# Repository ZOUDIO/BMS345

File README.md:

# BMS345
Protection and charging module for 3/4/5S lithium batteries 
This project is fully open-source and may be used commercially.
ZOUDIO is only liable for products of its own production.

Based on:
Texas Instruments BQ77915 primary battery protector
Texas Instruments BQ24650 battery charger

Configuration is set by using the onboard header. 

Specifications (for more details and instructions, refer to the PDF datasheet)
-	Overvoltage:				4.2V ±10mV, delay 1S
-	Undervoltage: 			2.9V ±18mV, delay 1S
-	Cell balancing 			4mA per cell
-	Maximum continuous discharge:	10A
-	Overcurrent protection: 		15A, delay 180mS
-	Short-circuit protection: 		30A, delay 1mS
-	Recovery after fault event: 		Attach charger
-	Open cell/wire detection:		4.5S delay
-	Power consumption: 			8μA typical
-	Charging current:			1A
-	Charging voltage:			4.05V per cell
-	MPPT voltage:			17.5V
-	Operating temperature: 		-40 to 85 °C
-	Dimensions (WxHxD):		71x38x15mm

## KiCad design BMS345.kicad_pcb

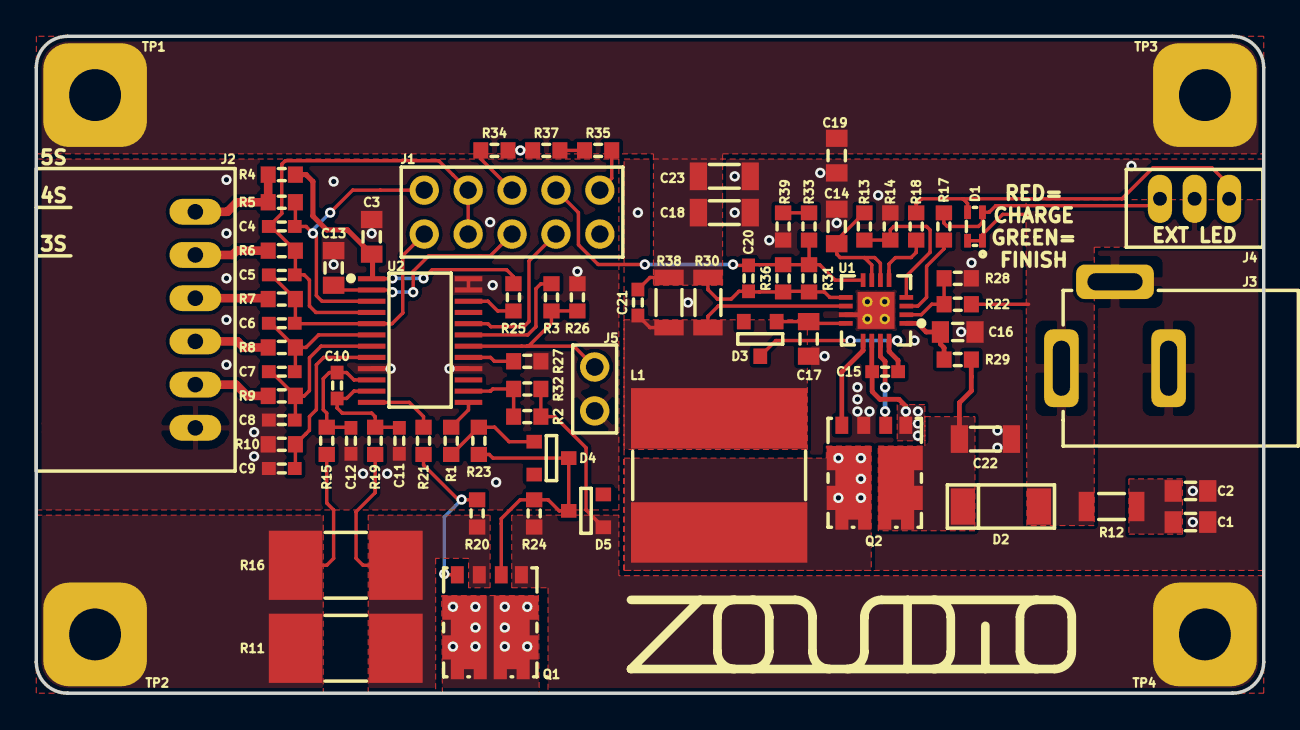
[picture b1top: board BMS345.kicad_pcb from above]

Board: 2 copper layers, 71.0 x 38.0 mm, 82 parts (0 on the bottom side), 54 nets.

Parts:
C1, C2, C3, C13, C14, C16, C17, C19: 1u; C0805
C4, C5, C6, C7, C8, C9, C10, C11, C12, C15, C21: 100n; C0603
C18, C22, C23: 10u; C1206
C20: 18p; C0603
D1: RED/GREEN; KingBright_KPTB
D2: Schottky; SOD-128
D3, D4: Schottky; SOT-23Z
D5: 10V; SOT-23Z
J1: CONFIG; PinHeader_2x05_P2.54mm_Vertical
J2: BATT; JSTXH_S6B
J3: DC Jack; DC_Jack
J4: EXTLED; JSTPH_3P
J5: NTC; 2P_2.54mm_header
L1: 10u; SRN1060
Logo1: ZOUDIO; ZOUDIO25mm
Q1, Q2: NMOS; SO8FLDual
R1, R3, R17, R18, R21, R25, R26: 10k; R0603
R2, R20, R22, R23, R31, R32: 1M; R0603
R4, R5, R6, R7, R8, R9, R10: 1K; R0603
R11, R16: 8m; R2512SNS
R12: 2R; R1206
R13, R14: 10K; R0603
R15, R19: 100R; R0603
R24: 3M3; R0603
R27, R33, R39: 100k; R0603
R28: 75K; R0603
R29: 10R; R0603
R30, R38: 39m; R1206
R34, R35, R37: 249k; R0603
R36: 33M; R0603
TP1: BATT+; Pad_6mm
TP2: BATT-; Pad_6mm
TP3: PACK+; Pad_6mm
TP4: PACK-; Pad_6mm
U1: BQ24650; QFN16
U2: BQ77915; TSSOP-24

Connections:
+24V: D1.1, D1.3, D2.2, J3.1, J4.2, R12.2, R22.2
/AVDD: C13.1, J1.6, U2.2
/BATT-: R11.2, R15.1, R16.2, TP2.1
/CCFG: J1.4, U2.20
/PACK+: C18.1, C19.2, C20.1, C21.2, C23.1, R30.2, R31.2, R36.2, R38.2, TP1.1, TP3.1, U1.9
/TS: R13.1, R14.2, U1.4
/VC3: C5.2, C6.1, J1.10, R7.1, U2.5
/VC4: C4.2, C5.1, J1.7, J1.8, R6.1, U2.4
/VC5: C4.1, J1.9, R5.1, U2.3
/VFB: C20.2, J1.3, R31.1, R33.2, R36.1, U1.8
/VREF: C14.2, R13.2, U1.6, U1.7
GND: C3.2, C8.2, C9.1, C11.1, C12.2, C13.2, J1.2, J2.1, J5.2, R10.2, R26.1, R27.1, U2.9, U2.16, U2.23, U2.24
GNDPWR: C1.1, C2.1, C14.1, C16.2, C17.2, C18.2, C19.1, C22.2, C23.2, D5.2, J3.2, J3.3, Q1.5, Q2.2, R2.1, R14.1, R24.1, R28.1, R32.1, R34.2, R37.2, R39.1, TP4.1, U1.11, U1.17
unnamed: C1.2, C2.2, R12.1
unnamed: C3.1, R4.1, R25.1, U2.1
unnamed: C6.2, C7.1, R8.1, U2.6
unnamed: C7.2, C8.1, R9.1, U2.7
unnamed: C9.2, R10.1, U2.8
unnamed: C10.1, C11.2, R19.2, U2.11
unnamed: C10.2, C12.1, R15.2, U2.10
unnamed: C15.1, D3.1, U1.16
unnamed: C15.2, L1.1, Q2.4, Q2.5, U1.14
unnamed: C16.1, R29.1, U1.1
unnamed: C17.1, D3.2, U1.12
unnamed: C21.1, L1.2, R30.1, R38.1, U1.10
unnamed: C22.1, D2.1, Q2.6, R29.2
unnamed: D1.2, J4.3, R17.2
unnamed: D1.4, J4.1, R18.2
unnamed: D4.1, D5.1, Q1.1, R23.1, R24.2
unnamed: D4.2, R1.1, R23.2
unnamed: J1.1, R35.1
unnamed: J1.5, R34.1
unnamed: J2.2, R9.2
unnamed: J2.3, R8.2
unnamed: J2.4, R7.2
unnamed: J2.5, R6.2
unnamed: J2.6, R4.2, R5.2
unnamed: J5.1, R3.1, R26.2, U2.18
unnamed: Q1.2, R11.1, R16.1, R19.1, R20.1
unnamed: Q1.3, R20.2, R21.1
unnamed: Q1.4, Q1.6
unnamed: Q2.1, U1.15
unnamed: Q2.3, U1.13
unnamed: R1.2, U2.13
unnamed: R2.2, R32.2, U2.14
unnamed: R3.2, U2.19
unnamed: R17.1, U1.3
unnamed: R18.1, U1.5
unnamed: R21.2, U2.12
unnamed: R22.1, R28.2, U1.2
unnamed: R25.2, U2.22
unnamed: R27.2, U2.17
unnamed: R33.1, R39.2
unnamed: R35.2, R37.1

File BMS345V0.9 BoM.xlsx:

Quantity | Designator | Package | Type | Value | MPFN
1 | U1 | SMD, QFN16 |  |  | BQ24650RVAR
1 | U2 | SMD, TSSOP-24 |  |  | BQ7791500PWR
2 | Q1,Q2 | SMD, SO8FL-dual | Dual NMOS |  | NVMFD5C466NLT1G
1 | D1 | SMD, 1.6x1.25mm | Bicolor LED | RED/GREEN | KPTB-1612SURKCGKC
1 | D2 | SMD, SOD-128 | Schottky |  | PMEG4050EP,115
2 | D3,D4 | SMD, SOT-23 | Schottky |  | BAT54C-7-F
1 | D5 | SMD, SOT-23 | Zener | 10V | BZX84C10LT1G
1 | L1 | SMD, 10x10mm | Shielded | 10u | SRN1060-100M
2 | R11,R16 | SMD, 2512 | 1% or better | 8m | MRF6432(2512)LR008FTS
1 | R30 | SMD, 1206 | 1% or better | 39m | STE1206M1W0R039F
1 | R12 | SMD, 1206 | 1% or better | 2R | 1206W4F200KT5E
1 | R29 | SMD, 0603 | 1% or better | 10R | 0603WAF100JT5E
2 | R15,R19 | SMD, 0603 | 1% or better | 100R | 0603WAF1000T5E
7 | R4,R5,R6,R7,R8,R9,R10 | SMD, 0603 | 1% or better | 1K | 0603WAF1001T5E
9 | R1,R3,R13,R14,R17,R18,R21,R25,R26 | SMD, 0603 | 1% or better | 10K | 0603WAF1002T5E
1 | R28 | SMD, 0603 | 1% or better | 75K | 0603WAF7502T5E
3 | R27,R33,R39 | SMD, 0603 | 1% or better | 100k | 0603WAF1003T5E
3 | R34,R35,R37 | SMD, 0603 | 1% or better | 249k | 0603WAF2493T5E
6 | R2,R20,R22,R23,R31,R32 | SMD, 0603 | 1% or better | 1M | 0603WAF1004T5E
1 | R24 | SMD, 0603 | 1% or better | 3M3 | 0603WAF3304T5E
1 | R36 | SMD, 0603 | 1% or better | 22M | RTT032205FTP
1 | C20 | SMD, 0603 | X5R and +/-20% or better, 50V+ | 18p | CC0603JRNPO9BN180
11 | C4,C5,C6,C7,C8,C9,C10,C11,C12,C15,C21 | SMD, 0603 | X5R and +/-20% or better, 50V+ | 100n | CC0603KRX7R9BB104
8 | C1,C2,C3,C13,C14,C16,C17,C19 | SMD, 0805 | X5R and +/-20% or better, 50V+ | 1u | CL21B105KBFNNNE
3 | C18,C22,C23 | SMD, 1206 | X5R and +/-20% or better, 50V+ | 10u | CL31B106KBHNNNE
1 | J1 | TH, 2.54mm pinheader | 2x5P |  | Z-21310110021001
All following components are Do Not Place (DNP):
DNP | R38 | SMD, 1206
DNP | J2 | TH, JSTXH_6P
DNP | J3 | TH, DC Jack
DNP | J4 | TH, JSTPH_3P
DNP | J5 | TH, Pinheader 1x2
DNP | Logo1 | Silkscreen logo
DNP | TP1, TP2, TP3, TP4 | Solderpad

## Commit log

2019-07-17 Added design files and datasheet
2019-07-17 Create gerber description
2019-07-17 Add gerber and PnP files
2022-03-31 Rename and fix symbol library reference
    Remove version number from names
    Fix symbol library references so schematic does not break for future viewers.
    Footprint library is still a mess, but they are cached in the layout, so it matters less.
2022-03-31 Add documentation and picture
2022-03-31 Add picture to readme
